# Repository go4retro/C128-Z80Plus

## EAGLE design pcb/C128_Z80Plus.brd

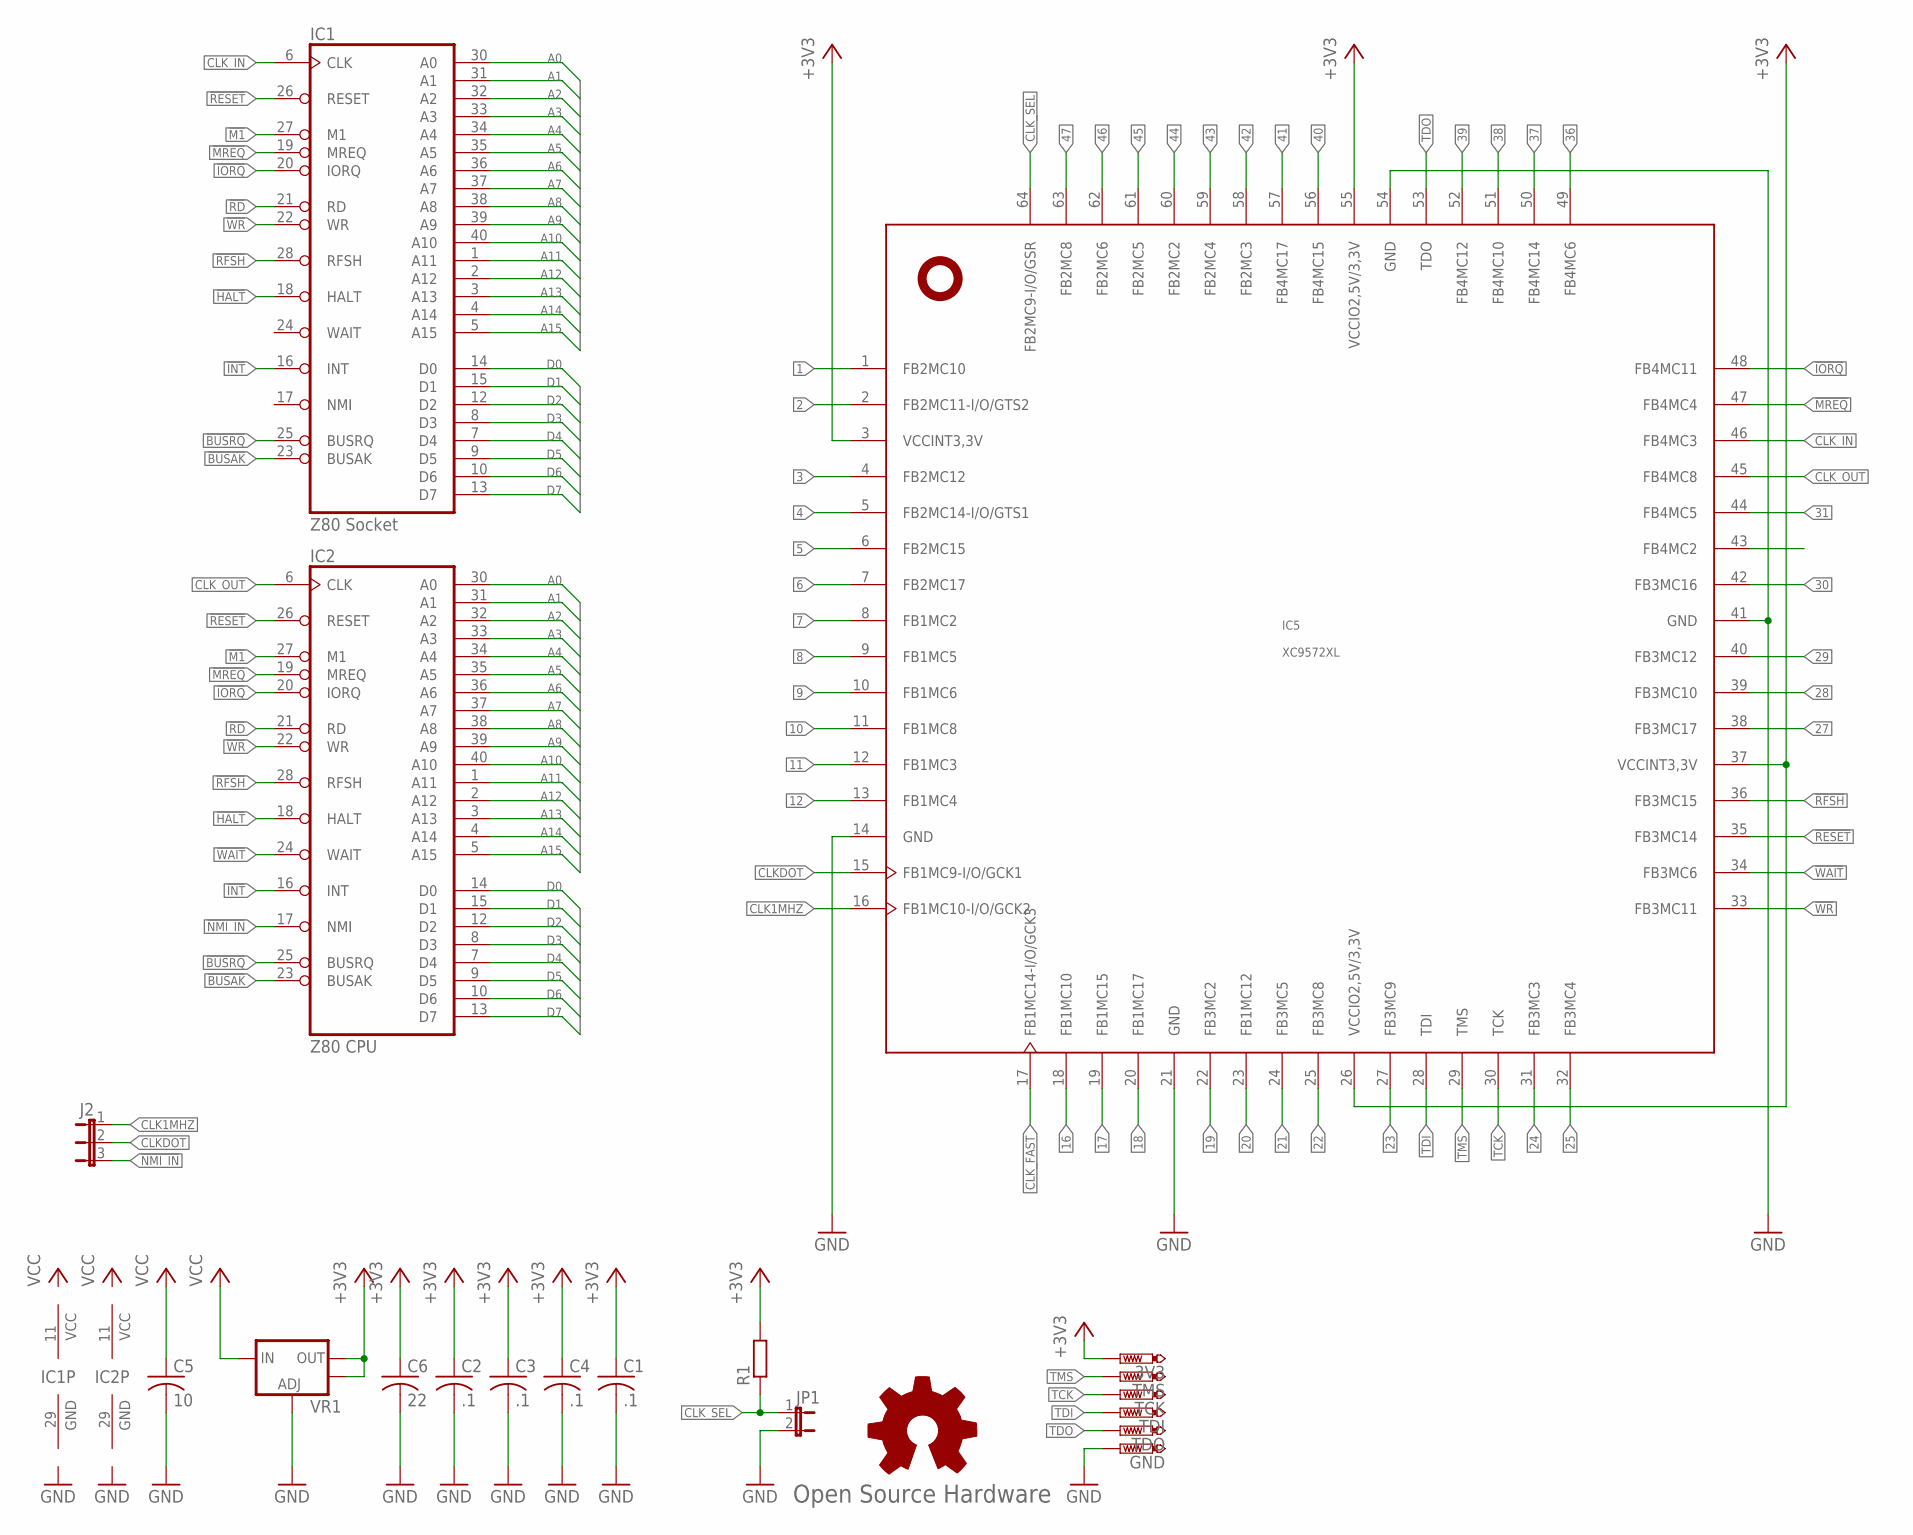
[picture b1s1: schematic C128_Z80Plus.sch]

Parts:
3V3: PTR1TP08R; TP08R
C1, C2, C3, C4: .1; C0402
C5: 10; C0805
C6: 22; C0805
GND: PTR1TP08R; TP08R
GOLD_ORB_SM1: Open Source Hardware; OSHW_5MM
IC1: Z80 Socket; DIL40-ROUNDPAD
IC2: Z80 CPU; DIL40-ROUNDPAD
IC5: XC9572XL; VQFP64
J2: JP2E; JP2
JP1: JP1E; JP1
R1: R-EU_R0402; R0402
TCK: PTR1TP08R; TP08R
TDI: PTR1TP08R; TP08R
TDO: PTR1TP08R; TP08R
TMS: PTR1TP08R; TP08R
VR1: V_REG_LM1117SOT223; SOT223

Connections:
1: IC5.1 (FB2MC10)
2: IC5.2 (FB2MC11-I/O/GTS2)
3: IC5.4 (FB2MC12)
4: IC5.5 (FB2MC14-I/O/GTS1)
5: IC5.6 (FB2MC15)
6: IC5.7 (FB2MC17)
7: IC5.8 (FB1MC2)
8: IC5.9 (FB1MC5)
9: IC5.10 (FB1MC6)
10: IC5.11 (FB1MC8)
11: IC5.12 (FB1MC3)
12: IC5.13 (FB1MC4)
16: IC5.18 (FB1MC10)
17: IC5.19 (FB1MC15)
18: IC5.20 (FB1MC17)
19: IC5.22 (FB3MC2)
20: IC5.23 (FB1MC12)
21: IC5.24 (FB3MC5)
22: IC5.25 (FB3MC8)
23: IC5.27 (FB3MC9)
24: IC5.31 (FB3MC3)
25: IC5.32 (FB3MC4)
27: IC5.38 (FB3MC17)
28: IC5.39 (FB3MC10)
29: IC5.40 (FB3MC12)
30: IC5.42 (FB3MC16)
31: IC5.44 (FB4MC5)
36: IC5.49 (FB4MC6)
37: IC5.50 (FB4MC14)
38: IC5.51 (FB4MC10)
39: IC5.52 (FB4MC12)
40: IC5.56 (FB4MC15)
41: IC5.57 (FB4MC17)
42: IC5.58 (FB2MC3)
43: IC5.59 (FB2MC4)
44: IC5.60 (FB2MC2)
45: IC5.61 (FB2MC5)
46: IC5.62 (FB2MC6)
47: IC5.63 (FB2MC8)
!BUSAK: IC1.23 (BUSAK), IC2.23 (BUSAK)
!BUSRQ: IC1.25 (BUSRQ), IC2.25 (BUSRQ)
!HALT: IC1.18 (HALT), IC2.18 (HALT)
!INT: IC1.16 (INT), IC2.16 (INT)
!IORQ: IC1.20 (IORQ), IC2.20 (IORQ), IC5.48 (FB4MC11)
!M1: IC1.27 (M1), IC2.27 (M1)
!MREQ: IC1.19 (MREQ), IC2.19 (MREQ), IC5.47 (FB4MC4)
!NMI_IN: IC2.17 (NMI), J2.3
!RD: IC1.21 (RD), IC2.21 (RD)
!RESET: IC1.26 (RESET), IC2.26 (RESET), IC5.35 (FB3MC14)
!RFSH: IC1.28 (RFSH), IC2.28 (RFSH), IC5.36 (FB3MC15)
!WAIT: IC2.24 (WAIT), IC5.34 (FB3MC6)
!WR: IC1.22 (WR), IC2.22 (WR), IC5.33 (FB3MC11)
+3V3: 3V3.TP, C1.1, C2.1, C3.1, C4.1, C6.1, IC5.3 (VCCINT3,3V), IC5.26 (VCCIO2,5V/3,3V), IC5.37 (VCCINT3,3V), IC5.55 (VCCIO2,5V/3,3V), R1.2, VR1.2 (OUT), VR1.4 (OUT)
A0: IC1.30 (A0), IC2.30 (A0)
A1: IC1.31 (A1), IC2.31 (A1)
A2: IC1.32 (A2), IC2.32 (A2)
A3: IC1.33 (A3), IC2.33 (A3)
A4: IC1.34 (A4), IC2.34 (A4)
A5: IC1.35 (A5), IC2.35 (A5)
A6: IC1.36 (A6), IC2.36 (A6)
A7: IC1.37 (A7), IC2.37 (A7)
A8: IC1.38 (A8), IC2.38 (A8)
A9: IC1.39 (A9), IC2.39 (A9)
A10: IC1.40 (A10), IC2.40 (A10)
A11: IC1.1 (A11), IC2.1 (A11)
A12: IC1.2 (A12), IC2.2 (A12)
A13: IC1.3 (A13), IC2.3 (A13)
A14: IC1.4 (A14), IC2.4 (A14)
A15: IC1.5 (A15), IC2.5 (A15)
CLK1MHZ: IC5.16 (FB1MC10-I/O/GCK2), J2.1
CLKDOT: IC5.15 (FB1MC9-I/O/GCK1), J2.2
CLK_FAST: IC5.17 (FB1MC14-I/O/GCK3)
CLK_IN: IC1.6 (CLK), IC5.46 (FB4MC3)
CLK_OUT: IC2.6 (CLK), IC5.45 (FB4MC8)
CLK_SEL: IC5.64 (FB2MC9-I/O/GSR), JP1.1, R1.1
D0: IC1.14 (D0), IC2.14 (D0)
D1: IC1.15 (D1), IC2.15 (D1)
D2: IC1.12 (D2), IC2.12 (D2)
D3: IC1.8 (D3), IC2.8 (D3)
D4: IC1.7 (D4), IC2.7 (D4)
D5: IC1.9 (D5), IC2.9 (D5)
D6: IC1.10 (D6), IC2.10 (D6)
D7: IC1.13 (D7), IC2.13 (D7)
GND: C1.2, C2.2, C3.2, C4.2, C5.2, C6.2, GND.TP, IC1.29 (GND), IC2.29 (GND), IC5.14 (GND), IC5.21 (GND), IC5.41 (GND), IC5.54 (GND), JP1.2, VR1.1 (ADJ)
PORT4: IC5.43 (FB4MC2)
TCK: IC5.30 (TCK), TCK.TP
TDI: IC5.28 (TDI), TDI.TP
TDO: IC5.53 (TDO), TDO.TP
TMS: IC5.29 (TMS), TMS.TP
VCC: C5.1, IC1.11 (VCC), IC2.11 (VCC), VR1.3 (IN)

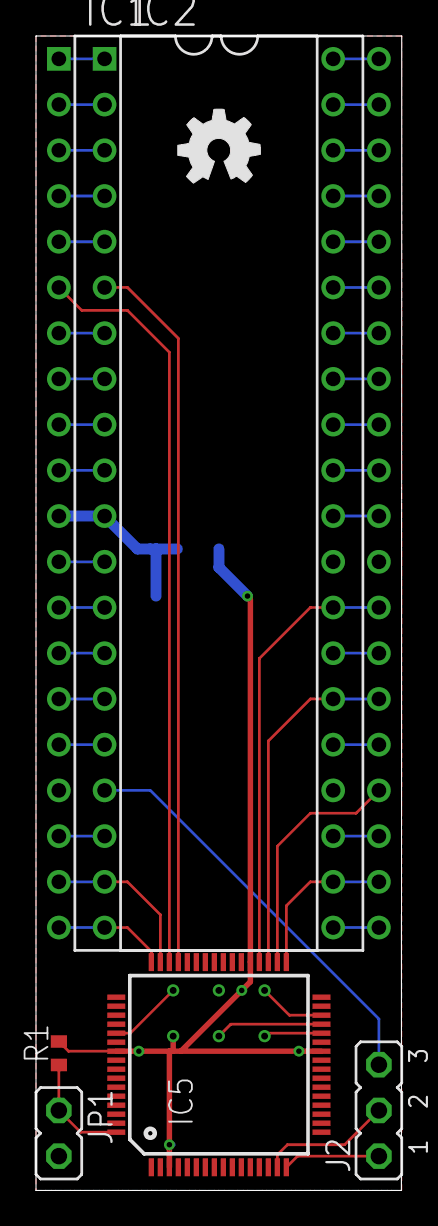
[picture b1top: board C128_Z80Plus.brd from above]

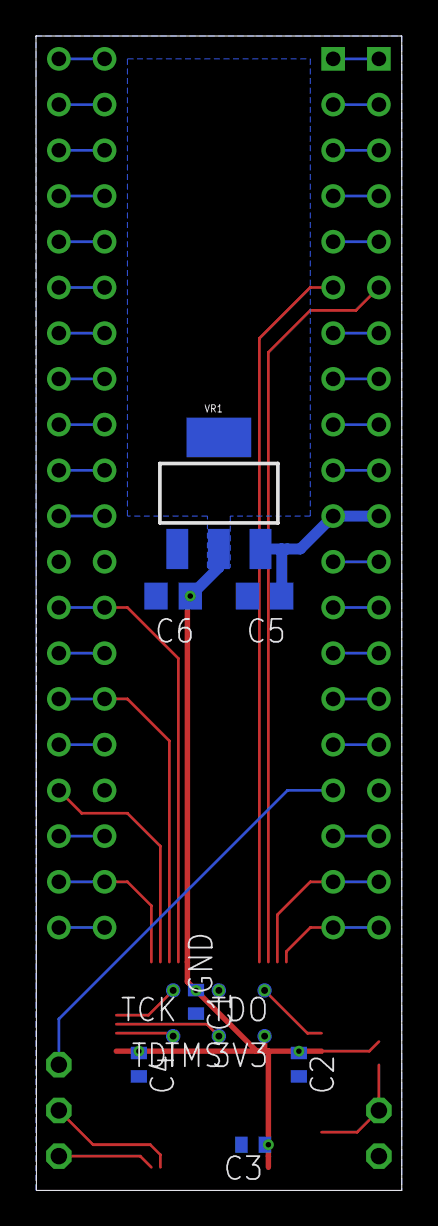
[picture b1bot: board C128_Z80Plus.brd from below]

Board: 2 copper layers, 20.3 x 64.1 mm, 20 parts (13 on the bottom side), 49 nets.

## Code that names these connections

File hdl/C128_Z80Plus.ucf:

#PACE: Start of Constraints generated by PACE

#PACE: Start of PACE I/O Pin Assignments
NET "CLK1MHZ"  LOC = "p16"  ;
NET "CLKDOT"  LOC = "p15"  ;
NET "CLKOUT"  LOC = "p45"  ;
NET "CLKZ80"  LOC = "p46"  ;
NET "CLOCKSEL"  LOC = "p64"  ;
NET "nIORQ"  LOC = "p48"  ;
NET "nMREQ"  LOC = "p47"  ;
NET "nRESET"  LOC = "p35"  ;
NET "nRFSH"  LOC = "P36"  ;
NET "nWR"  LOC = "p33"  ;
NET "WAIT"  LOC = "p34"  ;

#PACE: Start of PACE Area Constraints

#PACE: Start of PACE Prohibit Constraints

#PACE: End of Constraints generated by PACE

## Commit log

2024-06-06 Migrated GAL/FF to Xilinx xc9572xl HDL

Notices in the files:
parts and their libraries:
SparkFun: Licensing: CC v3.0 Share-Alike You are welcome to use this library for commercial purposes.
